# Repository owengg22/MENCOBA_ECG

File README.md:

# ECG Analog Front-End

**Biomedical instrumentation · Analog signal conditioning · STM32 interface**

A work-in-progress ECG circuit project exploring how a small differential electrode signal can be amplified, filtered, and conditioned for a microcontroller ADC. Designed in **KiCad 10** as part of my biomedical instrumentation learning and development.

## Design overview

```text
Electrode input → Input RC network → Differential amplifier
              → Filter stage → Attenuation & DC offset → ADC interface

Power: ±12 V analog supply + LM2596S-5 step-down stage
```

| Block | Design elements | Intended role |
| :--- | :--- | :--- |
| Electrode input | Connector and RC network | Receive the differential input and limit high-frequency content. |
| Amplifier | Three LM741 stages with an adjustable gain resistor | Amplify the differential signal before further conditioning. |
| Filter | Active filter stage and RC components | Shape the signal bandwidth; topology remains under review. |
| ADC conditioning | Resistor attenuation, DC offset, series resistor, and BAT54S clamp | Scale and shift the signal for the 3.3 V ADC interface, with clamp protection. |
| Power | External ±12 V supply and LM2596S-5 buck stage | Supply the analog circuit and provide a 5 V rail. |
| Microcontroller | Blue Pill interface | Provide a connection point for subsequent ADC acquisition work. |

## What this project explores

- Differential amplification and gain adjustment.
- Analog filtering before digitization.
- The distinction between DC offset, attenuation, and input clamping.
- Integrating analog circuitry, power conversion, and a microcontroller interface.
- Organizing a schematic and PCB layout as a reproducible KiCad project.

## Repository contents

| File | Contents |
| :--- | :--- |
| [ECG.kicad_pro](ECG.kicad_pro) | KiCad project settings. |
| [ECG.kicad_sch](ECG.kicad_sch) | Electrode input, analog stages, power supply, and ADC interface schematic. |
| [ECG.kicad_pcb](ECG.kicad_pcb) | PCB layout working file. |
| [ecg-schematic.png](ecg-schematic.png) | Schematic preview. |

## Open the design

1. Download or clone this repository.
2. Open `ECG.kicad_pro` in **KiCad 10**.
3. Open the schematic or PCB editor from the project manager.
4. Check symbol and footprint library resolution, including the Blue Pill symbol, before making fabrication outputs.

## Current status

**Design in progress.** The repository contains design files, not evidence of a validated ECG acquisition system. Measured gain, bandwidth, noise, and ADC performance are not yet documented here.

An earlier schematic review flagged the **U4 filter feedback topology** for correction or verification. Supply decoupling, gain selection, net connectivity, component ratings, and PCB layout also require verification before treating the design as complete.

This is an educational prototype, not a medical device. ADC clamping does not establish patient protection or isolation. Initial evaluation should use a signal source or ECG simulator rather than a person.

---

Part of my work in **biomedical instrumentation, embedded systems, and IoT telemetry**.

[Back to my profile](https://github.com/owengg22)

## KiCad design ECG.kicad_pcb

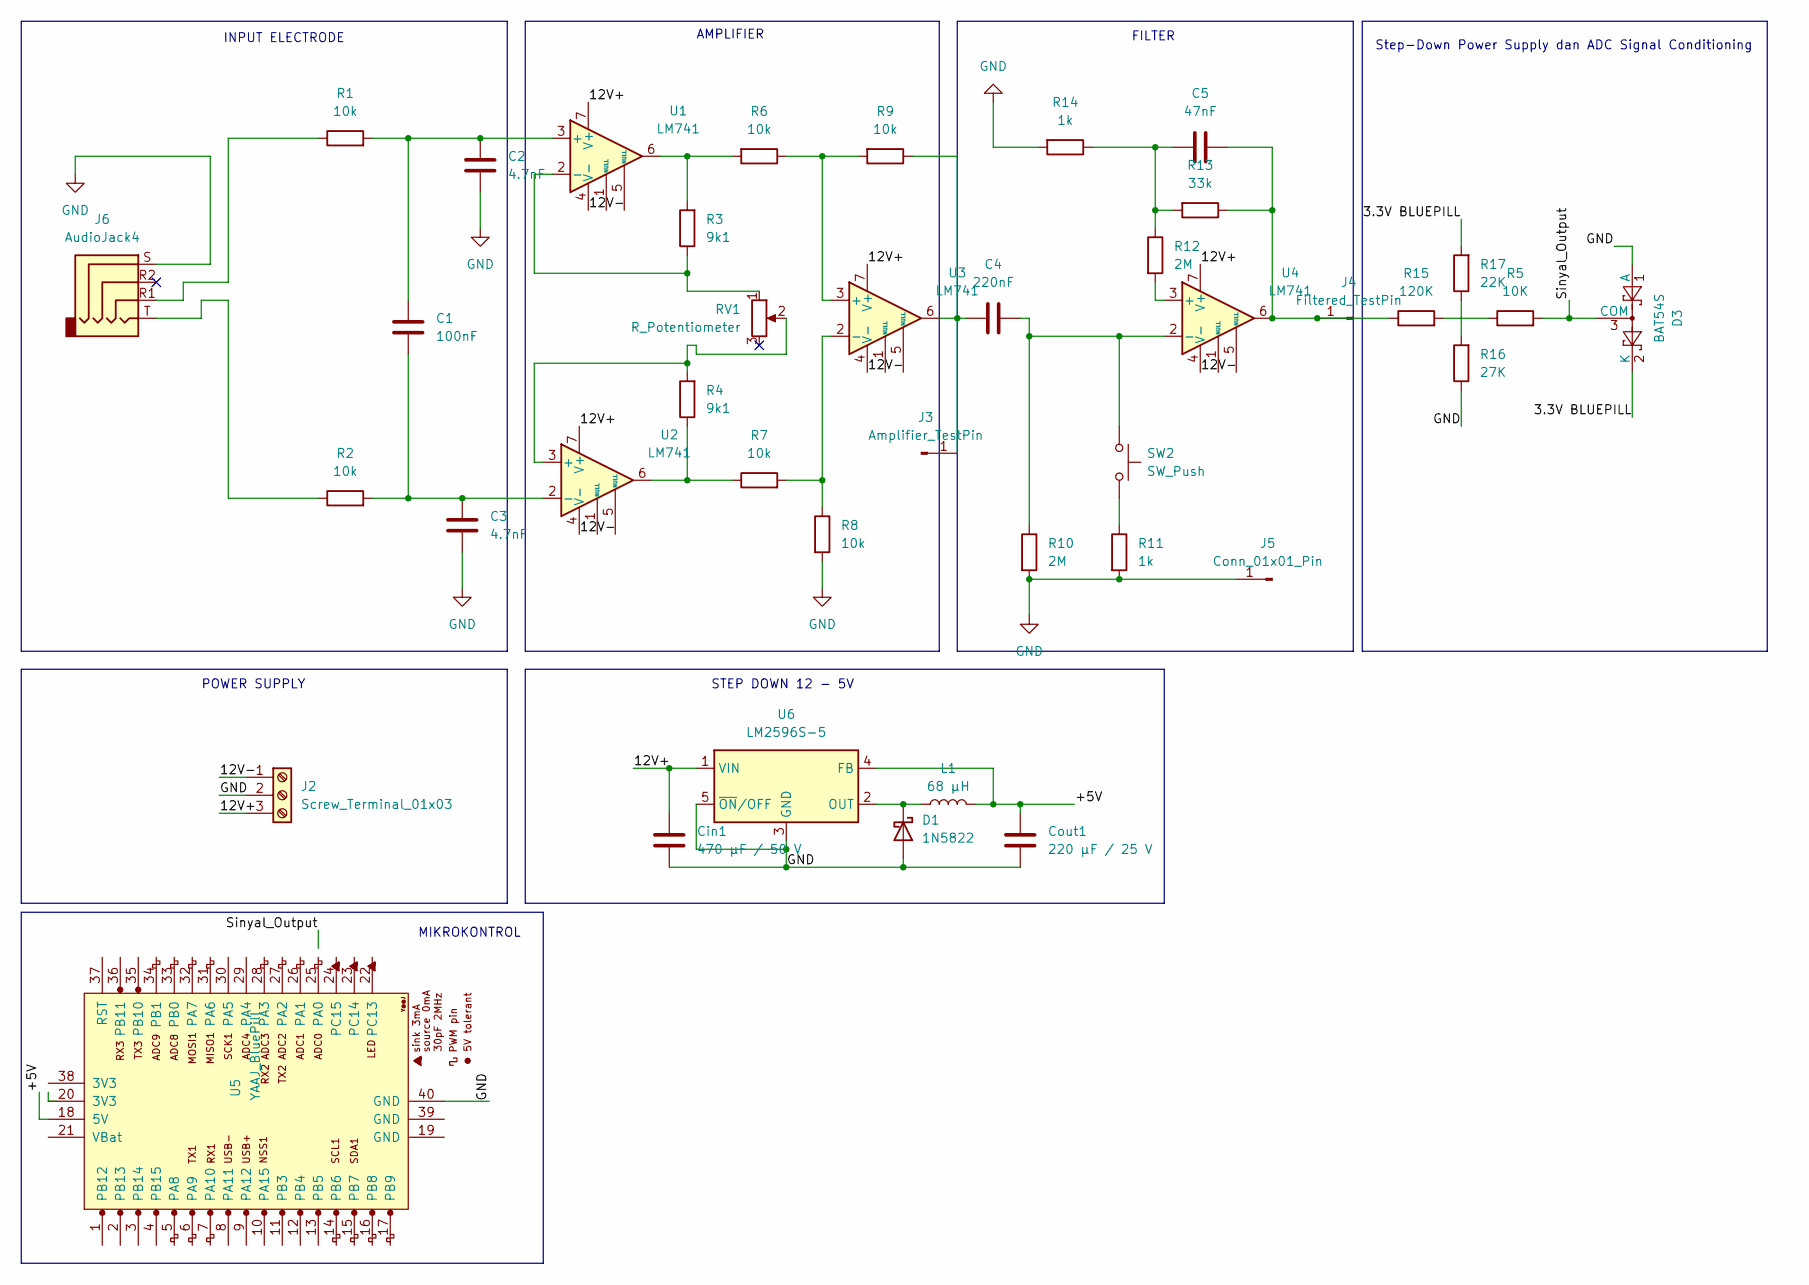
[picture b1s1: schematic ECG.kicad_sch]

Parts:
C1: 100nF; C_Disc_D5.0mm_W2.5mm_P5.00mm
C2, C3: 4.7nF; C_Disc_D5.0mm_W2.5mm_P5.00mm
C4: 220nF; C_Disc_D5.0mm_W2.5mm_P5.00mm
C5: 47nF; C_Disc_D5.0mm_W2.5mm_P5.00mm
Cin1: 470 µF / 50 V; CP_Radial_D10.0mm_P5.00mm
Cout1: 220 µF / 25 V; CP_Radial_D8.0mm_P3.50mm
D1: 1N5822; D_DO-201AD_P15.24mm_Horizontal
D3: BAT54S; SOT-23
J2: Screw_Terminal_01x03; TerminalBlock_MaiXu_MX126-5.0-03P_1x03_P5.00mm
J3: Amplifier_TestPin; PinHeader_1x01_P2.54mm_Vertical
J4: Filtered_TestPin; PinHeader_1x01_P2.54mm_Vertical
J5: Conn_01x01_Pin; PinHeader_1x01_P2.54mm_Vertical
J6: AudioJack4; Jack_3.5mm_PJ320D_Horizontal
L1: 68 µH; L_Radial_D10.0mm_P5.00mm_Fastron_07P
R1, R2, R6, R7, R8, R9: 10k; R_Axial_DIN0207_L6.3mm_D2.5mm_P7.62mm_Horizontal
R3, R4: 9k1; R_Axial_DIN0207_L6.3mm_D2.5mm_P7.62mm_Horizontal
R5: 10K; R_Axial_DIN0207_L6.3mm_D2.5mm_P7.62mm_Horizontal
R10, R12: 2M; R_Axial_DIN0207_L6.3mm_D2.5mm_P7.62mm_Horizontal
R11, R14: 1k; R_Axial_DIN0207_L6.3mm_D2.5mm_P7.62mm_Horizontal
R13: 33k; R_Axial_DIN0207_L6.3mm_D2.5mm_P7.62mm_Horizontal
R15: 120K; R_Axial_DIN0207_L6.3mm_D2.5mm_P7.62mm_Horizontal
R16: 27K; R_Axial_DIN0207_L6.3mm_D2.5mm_P7.62mm_Horizontal
R17: 22K; R_Axial_DIN0207_L6.3mm_D2.5mm_P7.62mm_Horizontal
RV1: R_Potentiometer; Potentiometer_Bourns_3296Y_Vertical
SW2: SW_Push; SW_PUSH_6mm
U1, U2, U3, U4: LM741; DIP-8_W7.62mm
U5: YAAJ_BluePill; YAAJ_BluePill_1
U6: LM2596S-5; TO-263-5_TabPin3

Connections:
/3.3V BLUEPILL: D3.2 (K), R17.2
/12V+: Cin1.2, J2.3, U1.7 (V+), U2.7 (V+), U3.7 (V+), U4.7 (V+), U6.1 (VIN)
/12V-: J2.1, U1.4 (V-), U2.4 (V-), U3.4 (V-), U4.4 (V-)
/+5V: Cout1.2, L1.2, U5.18 (5V), U6.4 (FB)
/Sinyal_Output: D3.3 (COM), R5.2, U5.25 (PA0)
GND: C2.2, C3.2, Cin1.1, Cout1.1, D1.2 (A), D3.1 (A), J2.2, J5.1 (Pin_1_1), J6.S, R8.2, R10.2, R11.2, R14.2, R16.1, U5.39 (GND), U5.40 (GND), U6.3 (GND), U6.5 (~ON/OFF)
unnamed: C5.1, R12.1, R13.2, R14.1
unnamed: D1.1 (K), L1.1, U6.2 (OUT)
unnamed: C4.1, J3.1 (Pin_1_1), R9.1, U3.6
unnamed: C5.2, J4.1 (Pin_1_1), R13.1, R15.1, U4.6
unnamed: J6.R1, R1.1
unnamed: J6.T, R2.1
unnamed: R3.2, R6.2, U1.6
unnamed: R4.1, R7.1, U2.6
unnamed: R11.1, SW2.2
unnamed: R5.1, R15.2
unnamed: R16.2, R17.1
unnamed: C1.1, C2.1, R1.2, U1.3 (+)
unnamed: R3.1, RV1.1, U1.2 (-)
unnamed: R4.2, RV1.2, U2.3 (+)
unnamed: C1.2, C3.1, R2.2, U2.2 (-)
unnamed: R6.1, R9.2, U3.3 (+)
unnamed: R7.2, R8.1, U3.2 (-)
unnamed: R12.2, U4.3 (+)
unnamed: C4.2, R10.1, SW2.1, U4.2 (-)

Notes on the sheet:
INPUT ELECTRODE
POWER SUPPLY
AMPLIFIER
FILTER
Step-Down Power Supply dan ADC Signal Conditioning
STEP DOWN 12 - 5V
MIKROKONTROL

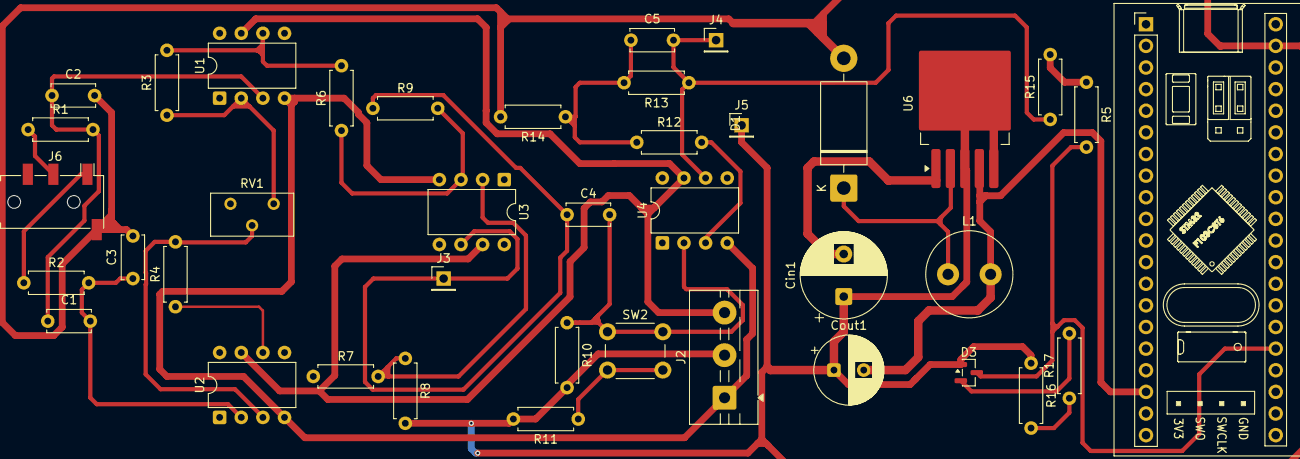
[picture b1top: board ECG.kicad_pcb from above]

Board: 2 copper layers, 40 parts (0 on the bottom side), 25 nets.
